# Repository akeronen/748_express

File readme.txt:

This repository contains:
	
	748 concept case with keycaps (Copyright © Ari Keronen 2023)

Remix of project:
	https://www.msx.org/wiki/Omega_MSX

Repository contained files:
		concept_748.STL
		keycaps.STL
		748-Keyboard.kicad_pcb
		748-Keyboard.kicad_pro
		748-Mainboard.kicad_pcb
		748-Mainboard.kicad_pro

are licensed under a Creative Commons license Attribution-ShareAlike 4.0 
International (CC BY-SA 4.0)??creativecommons.org/licenses/by-sa/4.0/deed.en_US

*******************************************************************************************
Disclaimer:

Above mentioned files have not been tested with any any kind of 3d printing / 2d printing.
Above mentioned files have not been electronically tested or validated.
Some autorouting of pcbs have been used and not tested with manufactured pcbs.
Lots of specifics are missing by design.
Usage is only allowed by own discretion and no liability of any kind can be bring forth
to its original creator.

*******************************************************************************************

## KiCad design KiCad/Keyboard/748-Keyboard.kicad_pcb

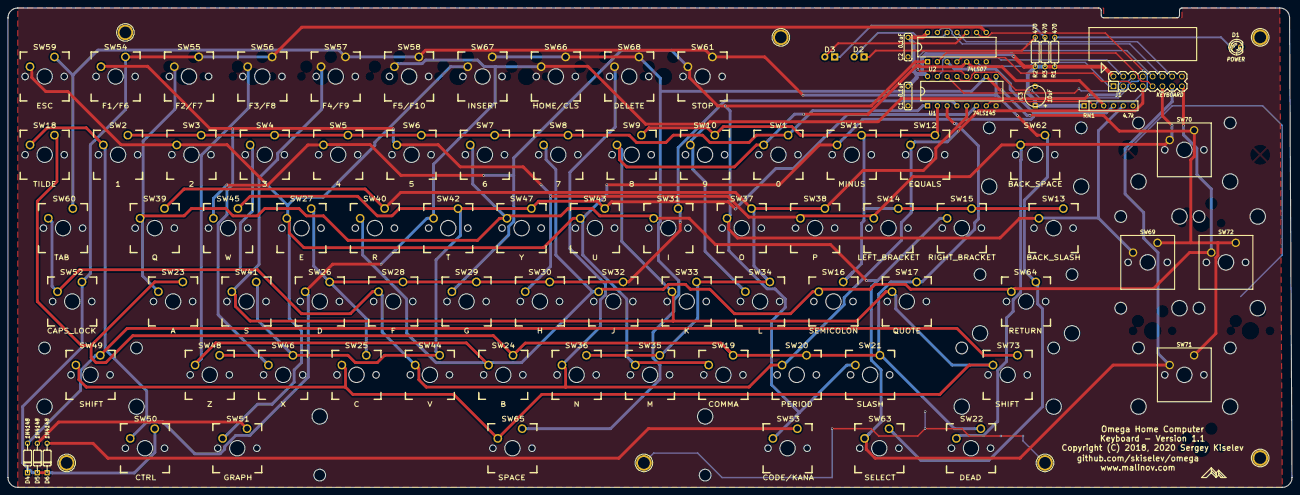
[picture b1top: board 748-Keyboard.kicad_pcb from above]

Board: 2 copper layers, 333.4 x 124.5 mm, 96 parts (0 on the bottom side), 37 nets.

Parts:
C1, C2: 0.1uF; Cap_Cer_508
C3: 10uF; Cap_Tant_508
D1: POWER; LED_3mm
D2: CAPS; CHERRY_MX_LED
D3: KANA; CHERRY_MX_LED
D4, D5, D6: 1N4148; Diode_762
HOLE1, HOLE2, HOLE3, HOLE4, HOLE5, HOLE6, HOLE7: HOLE; Hole_3mm
J1: KEYBOARD; Conn_Pin_Header_8x2_2.54mm
R1, R2, R3: 470; Res_762
RN1: 4.7k; Conn_SIL6
SW1: 0; CHERRY_PCB_100H
SW2: 1; CHERRY_PCB_100H
SW3: 2; CHERRY_PCB_100H
SW4: 3; CHERRY_PCB_100H
SW5: 4; CHERRY_PCB_100H
SW6: 5; CHERRY_PCB_100H
SW7: 6; CHERRY_PCB_100H
SW8: 7; CHERRY_PCB_100H
SW9: 8; CHERRY_PCB_100H
SW10: 9; CHERRY_PCB_100H
SW11: MINUS; CHERRY_PCB_100H
SW12: EQUALS; CHERRY_PCB_100H
SW13: BACK_SLASH; CHERRY_PCB_150H
SW14: LEFT_BRACKET; CHERRY_PCB_100H
SW15: RIGHT_BRACKET; CHERRY_PCB_100H
SW16: SEMICOLON; CHERRY_PCB_100H
SW17: QUOTE; CHERRY_PCB_100H
SW18: TILDE; CHERRY_PCB_100H
SW19: COMMA; CHERRY_PCB_100H
SW20: PERIOD; CHERRY_PCB_100H
SW21: SLASH; CHERRY_PCB_100H
SW22: DEAD; CHERRY_PCB_125H
SW23: A; CHERRY_PCB_100H
SW24: B; CHERRY_PCB_100H
SW25: C; CHERRY_PCB_100H
SW26: D; CHERRY_PCB_100H
SW27: E; CHERRY_PCB_100H
SW28: F; CHERRY_PCB_100H
SW29: G; CHERRY_PCB_100H
SW30: H; CHERRY_PCB_100H
SW31: I; CHERRY_PCB_100H
SW32: J; CHERRY_PCB_100H
SW33: K; CHERRY_PCB_100H
SW34: L; CHERRY_PCB_100H
SW35: M; CHERRY_PCB_100H
SW36: N; CHERRY_PCB_100H
SW37: O; CHERRY_PCB_100H
SW38: P; CHERRY_PCB_100H
SW39: Q; CHERRY_PCB_100H
SW40: R; CHERRY_PCB_100H
SW41: S; CHERRY_PCB_100H
SW42: T; CHERRY_PCB_100H
SW43: U; CHERRY_PCB_100H
SW44: V; CHERRY_PCB_100H
SW45: W; CHERRY_PCB_100H
SW46: X; CHERRY_PCB_100H
SW47: Y; CHERRY_PCB_100H
SW48: Z; CHERRY_PCB_100H
SW49: SHIFT; CHERRY_PCB_225H
SW50: CTRL; CHERRY_PCB_125H
SW51: GRAPH; CHERRY_PCB_125H
SW52: CAPS_LOCK; CHERRY_PCB_175H
SW53: CODE/KANA; CHERRY_PCB_125H
SW54: F1/F6; CHERRY_PCB_100H
SW55: F2/F7; CHERRY_PCB_100H
SW56: F3/F8; CHERRY_PCB_100H
SW57: F4/F9; CHERRY_PCB_100H
SW58: F5/F10; CHERRY_PCB_100H
SW59: ESC; CHERRY_PCB_100H
SW60: TAB; CHERRY_PCB_150H
SW61: STOP; CHERRY_PCB_100H
SW62: BACK_SPACE; CHERRY_PCB_200H
SW63: SELECT; CHERRY_PCB_125H
SW64: RETURN; CHERRY_PCB_225H
SW65: SPACE; CHERRY_PCB_625H
SW66: HOME/CLS; CHERRY_PCB_100H
SW67: INSERT; CHERRY_PCB_100H
SW68: DELETE; CHERRY_PCB_100H
SW69: LEFT; SW_Cherry_MX_2.00u_Vertical_PCB
SW70: UP; SW_Cherry_MX_2.00u_PCB
SW71: DOWN; SW_Cherry_MX_2.00u_PCB
SW72: RIGHT; SW_Cherry_MX_2.00u_Vertical_PCB
SW73: SHIFT; CHERRY_PCB_275H
U1: 74LS145; IC_DIP16_300
U2: 74LS07; IC_DIP14_300

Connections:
/CAPS_LED: J1.12, U2.13
/CAPS_LED_BUFFERED: D2.1 (K), U2.12
/CODE: D6.2 (A), SW53.1
/COLUMN0: RN1.3 (R2), SW1.2, SW9.2, SW17.2, SW25.2, SW33.2, SW41.2, SW49.2, SW57.2, SW65.2, SW73.2, U2.5
/COLUMN0_BUF: J1.1, U2.6
/COLUMN1: J1.3, SW2.2, SW10.2, SW18.2, SW26.2, SW34.2, SW42.2, SW50.2, SW58.2, SW66.2
/COLUMN2: RN1.4 (R3), SW3.2, SW11.2, SW19.2, SW27.2, SW35.2, SW43.2, SW51.2, SW59.2, SW67.2, U2.3
/COLUMN2_BUF: J1.5, U2.4
/COLUMN3: J1.7, SW4.2, SW12.2, SW20.2, SW28.2, SW36.2, SW44.2, SW52.2, SW60.2, SW68.2
/COLUMN4: RN1.5 (R4), SW5.2, SW13.2, SW21.2, SW29.2, SW37.2, SW45.2, SW53.2, SW61.2, SW69.2, U2.1
/COLUMN4_BUF: J1.9, U2.2
/COLUMN5: J1.11, SW6.2, SW14.2, SW22.2, SW30.2, SW38.2, SW46.2, SW54.2, SW62.2, SW70.2
/COLUMN6: J1.13, SW7.2, SW15.2, SW23.2, SW31.2, SW39.2, SW47.2, SW55.2, SW63.2, SW71.2
/COLUMN7: J1.15, SW8.2, SW16.2, SW24.2, SW32.2, SW40.2, SW48.2, SW56.2, SW64.2, SW72.2
/D1+: D1.2 (A), R1.2
/D2+: D2.2 (A), R2.2
/D3+: D3.2 (A), R3.2
/GRAPH: D5.2 (A), SW51.1
/KANA_LED: J1.14, U2.11
/KANA_LED_BUFFERED: D3.1 (K), U2.10
/ROW0: SW1.1, SW2.1, SW3.1, SW4.1, SW5.1, SW6.1, SW7.1, SW8.1, U1.1 (Q0)
/ROW1: SW9.1, SW10.1, SW11.1, SW12.1, SW13.1, SW14.1, SW15.1, SW16.1, U1.2 (Q1)
/ROW2: SW17.1, SW18.1, SW19.1, SW20.1, SW21.1, SW22.1, SW23.1, SW24.1, U1.3 (Q2)
/ROW3: SW25.1, SW26.1, SW27.1, SW28.1, SW29.1, SW30.1, SW31.1, SW32.1, U1.4 (Q3)
/ROW4: SW33.1, SW34.1, SW35.1, SW36.1, SW37.1, SW38.1, SW39.1, SW40.1, U1.5 (Q4)
/ROW5: SW41.1, SW42.1, SW43.1, SW44.1, SW45.1, SW46.1, SW47.1, SW48.1, U1.6 (Q5)
/ROW6: D4.1 (K), D5.1 (K), D6.1 (K), SW50.1, SW52.1, SW54.1, SW55.1, SW56.1, U2.8
/ROW6_UNBUF: RN1.2 (R1), U1.7 (Q6), U2.9
/ROW7: SW57.1, SW58.1, SW59.1, SW60.1, SW61.1, SW62.1, SW63.1, SW64.1, U1.9 (Q7)
/ROW8: SW65.1, SW66.1, SW67.1, SW68.1, SW69.1, SW70.1, SW71.1, SW72.1, U1.10 (Q8)
/ROW_A: J1.4, U1.15 (P0)
/ROW_B: J1.6, U1.14 (P1)
/ROW_C: J1.8, U1.13 (P2)
/ROW_D: J1.10, U1.12 (P3)
/SHIFT: D4.2 (A), SW49.1, SW73.1
GND: C1.2, C2.2, C3.2, D1.1 (K), HOLE1.1, HOLE2.1, HOLE3.1, HOLE4.1, HOLE5.1, HOLE6.1, HOLE7.1, J1.16, U1.8 (GND), U2.7 (GND)
VCC: C1.1, C2.1, C3.1, J1.2, R1.1, R2.1, R3.1, RN1.1 (common), U1.16 (VCC), U2.14 (VCC)

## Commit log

2023-05-20 Add files via upload
    License is in the "readme.txt" file.

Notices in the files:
KiCad/Keyboard/748-Keyboard.kicad_pcb:
Copyright (C) 2018, 2020 Sergey Kiselev
